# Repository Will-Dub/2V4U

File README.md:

# 2V4U

VCU, dashboard and documentation for an electric go-kart

## Overview

```
Software/            Dashboard and VCU code
Software/Dashboard   Qt dashboard
Software/VCU         VCU for an STM32G431
Software/VCU/Tests   Unit and integration tests
Hardware/            Schema of the VCU board
Docs/                Diagram and wiring
```

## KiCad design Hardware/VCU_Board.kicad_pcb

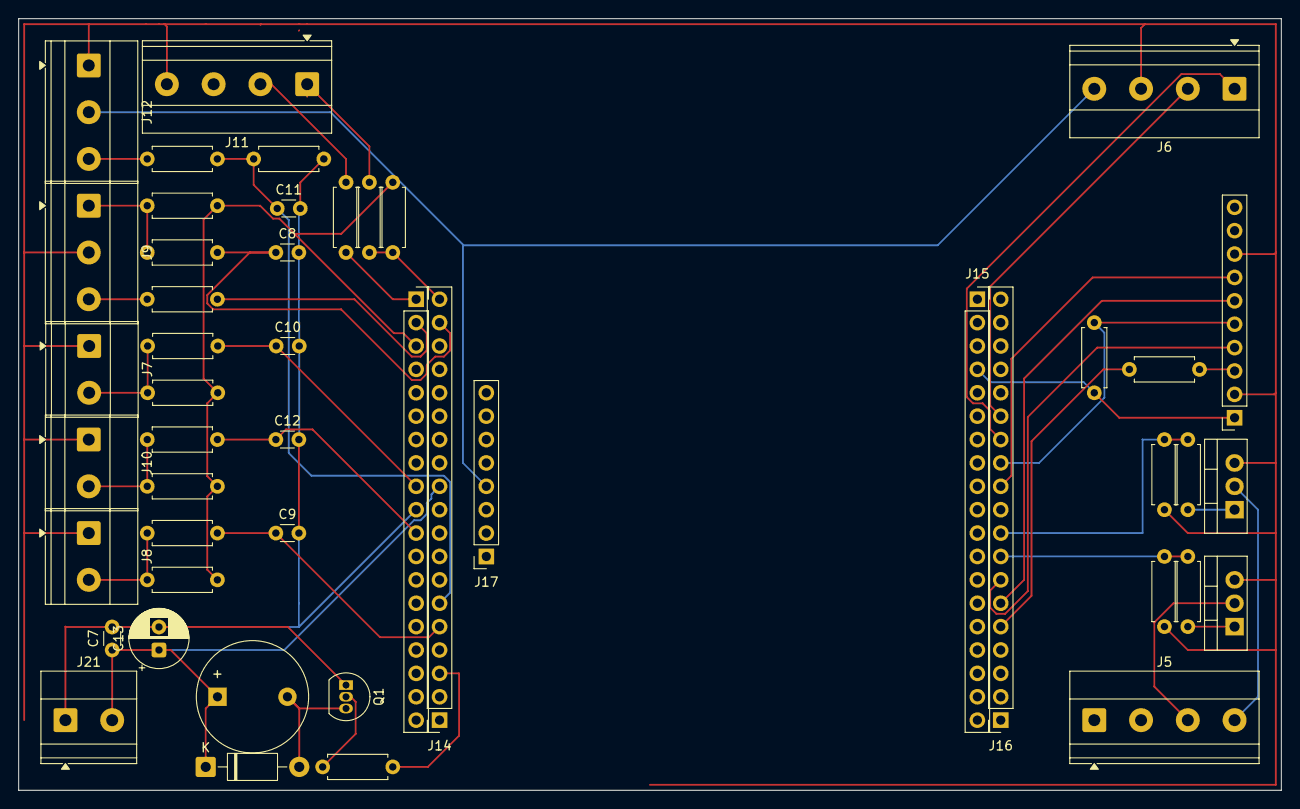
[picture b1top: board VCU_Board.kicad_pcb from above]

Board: 2 copper layers, 137.2 x 83.8 mm, 48 parts (0 on the bottom side), 36 nets.

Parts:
BZ1: Buzzer; Buzzer_12x9.5RM7.6
C7: 0.1μ; C_Disc_D3.0mm_W1.6mm_P2.50mm
C8, C9, C10, C11, C12: 100n; C_Disc_D3.0mm_W1.6mm_P2.50mm
C13: 10μ; CP_Radial_D6.3mm_P2.50mm
D4: D; D_DO-41_SOD81_P10.16mm_Horizontal
J3: ICM-20948; PinSocket_1x10_P2.54mm_Vertical
J5: Power Connector; TerminalBlock_Phoenix_MKDS-1,5-4-5.08_1x04_P5.08mm_Horizont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
J6: CAN Connector; TerminalBlock_Phoenix_MKDS-1,5-4-5.08_1x04_P5.08mm_Horizont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
J7: Direction Connector; TerminalBlock_Phoenix_MKDS-1,5-2-5.08_1x02_P5.08mm_Horizont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
J8: Brake Connector; TerminalBlock_Phoenix_MKDS-1,5-2-5.08_1x02_P5.08mm_Horizont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
J9: Sw Start Connector; TerminalBlock_Phoenix_MKDS-1,5-3-5.08_1x03_P5.08mm_Horizont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
J10: Emergency NO Connector; TerminalBlock_Phoenix_MKDS-1,5-2-5.08_1x02_P5.08mm_Horizont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
J11: BMS Connector; TerminalBlock_Phoenix_MKDS-1,5-4-5.08_1x04_P5.08mm_Horizont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
J12: Throttle Connector; TerminalBlock_Phoenix_MKDS-1,5-3-5.08_1x03_P5.08mm_Horizont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
J13, J14, J15, J16: Conn_01x19; PinSocket_1x19_P2.54mm_Vertical
J17: Conn_01x08; PinSocket_1x08_P2.54mm_Vertical
J21: Supply Connector; TerminalBlock_Phoenix_MKDS-1,5-2-5.08_1x02_P5.08mm_Horizont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
Q1: PN2222A; TO-92_Inline
Q3, Q4: MOSFET_CONTACTOR; TO-220-3_Vertical
R2, R20: 10000; R_Axial_DIN0207_L6.3mm_D2.5mm_P7.62mm_Horizontal
R3: 20000; R_Axial_DIN0207_L6.3mm_D2.5mm_P7.62mm_Horizontal
R4, R5, R6, R7, R19: 1000; R_Axial_DIN0207_L6.3mm_D2.5mm_P7.62mm_Horizontal
R8, R11, R13: 10k; R_Axial_DIN0207_L6.3mm_D2.5mm_P7.62mm_Horizontal
R9: 33; R_Axial_DIN0207_L6.3mm_D2.5mm_P7.62mm_Horizontal
R10: 270; R_Axial_DIN0207_L6.3mm_D2.5mm_P7.62mm_Horizontal
R12, R14: 100; R_Axial_DIN0207_L6.3mm_D2.5mm_P7.62mm_Horizontal
R15, R16, R17, R18: 2200; R_Axial_DIN0207_L6.3mm_D2.5mm_P7.62mm_Horizontal
R21, R22: 220; R_Axial_DIN0207_L6.3mm_D2.5mm_P7.62mm_Horizontal

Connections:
+3.3V: J3.1 (VCC), J13.3, J14.12, J15.4, J17.5, R4.1, R5.1, R6.1, R7.1, R8.1, R20.2
+5V: BZ1.1 (+), C7.1, C13.1, D4.1 (K), J6.4, J12.2, J14.11, J17.4, J21.2
/Driver/MOSFET_CONTACTOR_DRAIN: J5.3, Q4.2 (D)
/Driver/MOSFET_CONTACTOR_GATE: J16.8, R13.2, R14.1
/Driver/MOSFET_PRECHARGE_DRAIN: J5.4, Q3.2 (D)
/Driver/MOSFET_PRECHARGE_GATE: J16.9, R11.2, R12.1
/Interfaces/BMS_RX: J14.19, R20.1, R21.2
/Interfaces/BMS_TX: J13.1, R22.2
/Interfaces/BUZZER: J14.3, R19.2
/Interfaces/IMU_INT: J3.7 (INT), J16.11
/Interfaces/LED_SW_START: J13.2, R10.2
/Interfaces/SPI2_IMU_NCS: J3.5 (NCS), J16.12, R8.2
/Interfaces/SPI2_MISO: J3.6 (SDO), J16.6
/Interfaces/SPI2_MOSI: J3.4 (SDI), J16.7
/Interfaces/SPI2_SCK: J16.5, R9.1
/Interfaces/SW_BRAKE: C9.1, J14.5, R16.2
/Interfaces/SW_DIRECTION: C10.1, J13.9, R17.2
/Interfaces/SW_PUSH_EMERGENCY: C12.1, J13.11, R18.2
/Interfaces/SW_START: C8.1, J14.18, R15.1
/Interfaces/THROTTLE_ADC: C11.1, J14.6, R2.1, R3.1
/Off board high voltage/CAN_RX: J6.1, J16.13
/Off board high voltage/CAN_TX: J6.2, J16.14
GND: C7.2, C8.2, C9.2, C10.2, C11.2, C12.2, C13.2, J3.2 (GND), J3.8 (FSY), J6.3, J7.1, J8.1, J9.2, J10.1, J11.4, J12.1, J13.10, J14.9, J14.10, J14.16, J15.5, J16.4, J16.10, J17.2, J17.3, J21.1, Q1.1 (E), Q3.3 (S), Q4.3 (S), R3.2, R11.1, R13.1
unnamed: BZ1.2 (-), D4.2 (A), Q1.3 (C)
unnamed: J3.3 (SCLK), R9.2
unnamed: J7.2, R7.2, R17.1
unnamed: J8.2, R6.2, R16.1
unnamed: J9.1, R4.2, R15.2
unnamed: J9.3, R10.1
unnamed: J10.2, R5.2, R18.1
unnamed: J11.1, R21.1
unnamed: J11.2, R22.1
unnamed: J12.3, R2.2
unnamed: Q1.2 (B), R19.1
unnamed: Q3.1 (G), R12.2
unnamed: Q4.1 (G), R14.2

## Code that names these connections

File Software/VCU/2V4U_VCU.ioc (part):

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Mcu.Name=STM32G431R(6-8-B)Tx
Mcu.Package=LQFP64
Mcu.UserName=STM32G431RBTx
PA0.GPIOParameters=GPIO_Label
PA0.GPIO_Label=THROTTLE_ADC
PA0.Mode=IN1-Single-Ended
PA0.Signal=ADC1_IN1
PA1.GPIOParameters=GPIO_PuPd,GPIO_Label
PA1.GPIO_Label=SW_BRAKE
PA1.GPIO_PuPd=GPIO_PULLUP
PA1.Signal=GPIO_Input
PA11.GPIOParameters=GPIO_Label
PA11.GPIO_Label=CAN_RX
PA11.Mode=FDCAN_Activate
PA11.Signal=FDCAN1_RX
PA12.GPIOParameters=GPIO_Label
PA12.GPIO_Label=CAN_TX
PA12.Mode=FDCAN_Activate
PA12.Signal=FDCAN1_TX
PA13.GPIOParameters=GPIO_Label
PA13.GPIO_Label=T_SWDIO
PA13.Signal=SYS_JTMS-SWDIO
PA14.GPIOParameters=GPIO_Label
PA14.GPIO_Label=T_SWCLK
PA14.Signal=SYS_JTCK-SWCLK
PA15.GPIOParameters=GPIO_PuPd,GPIO_Label
PA15.GPIO_Label=SW_DIRECTION
PA15.GPIO_PuPd=GPIO_PULLUP
PA15.Signal=GPIO_Input
PA2.Mode=Asynchronous
PA2.Signal=LPUART1_TX
PA3.Mode=Asynchronous
PA3.Signal=LPUART1_RX
PA5.GPIOParameters=GPIO_Label
PA5.GPIO_Label=LED_BOARD
PA5.Signal=GPIO_Output
PB0.GPIOParameters=GPIO_Label
PB0.GPIO_Label=BUZZER
PB0.Signal=GPIO_Output
PB1.GPIOParameters=GPIO_Label
PB1.GPIO_Label=MOSFET_CONTACTOR_GATE
PB1.Signal=GPIO_Output
PB11.GPIOParameters=GPIO_Label
PB11.GPIO_Label=IMU_INT
PB11.Signal=GPXTI11
PB12.GPIOParameters=GPIO_Speed,PinState,GPIO_PuPd,GPIO_Label
PB12.GPIO_Label=SPI2_IMU_NCS
PB12.GPIO_PuPd=GPIO_PULLUP
PB12.GPIO_Speed=GPIO_SPEED_FREQ_VERY_HIGH
PB12.PinState=GPIO_PIN_SET
PB12.Signal=GPIO_Output
PB13.Mode=Full_Duplex_Master
PB13.Signal=SPI2_SCK
PB14.Mode=Full_Duplex_Master
PB14.Signal=SPI2_MISO
PB15.Mode=Full_Duplex_Master
PB15.Signal=SPI2_MOSI
PB2.GPIOParameters=GPIO_Label
PB2.GPIO_Label=MOSFET_PRECHARGE_GATE
PB2.Signal=GPIO_Output
PB3.GPIOParameters=GPIO_Label
PB3.GPIO_Label=T_SWO
PB3.Signal=SYS_JTDO-SWO
PB7.GPIOParameters=GPIO_PuPd,GPIO_Label
PB7.GPIO_Label=SW_PUSH_EMERGENCY
PB7.GPIO_PuPd=GPIO_PULLUP
PB7.Signal=GPIO_Input
PC10.GPIOParameters=GPIO_Label
PC10.GPIO_Label=BMS_TX
PC10.Mode=Asynchronous
PC10.Signal=UART4_TX
PC11.GPIOParameters=GPIO_Label
PC11.GPIO_Label=BMS_RX
PC11.Mode=Asynchronous
PC11.Signal=UART4_RX
PC12.GPIOParameters=GPIO_Label
PC12.GPIO_Label=LED_SW_START
PC12.Signal=GPIO_Output
PC13.GPIOParameters=GPIO_PuPd,GPIO_Label
PC13.GPIO_Label=BTN_BOARD
PC13.GPIO_PuPd=GPIO_PULLDOWN
PC13.Signal=GPIO_Input
PC14-OSC32_IN.GPIOParameters=GPIO_Label
PC14-OSC32_IN.GPIO_Label=RCC_OSC32_OUT
PC14-OSC32_IN.Signal=RCC_OSC32_IN
PC15-OSC32_OUT.GPIOParameters=GPIO_Label
PC15-OSC32_OUT.GPIO_Label=RCC_OSC32_OUT
PC15-OSC32_OUT.Signal=RCC_OSC32_OUT
PD2.GPIOParameters=GPIO_PuPd,GPIO_Label
PD2.GPIO_Label=SW_START
PD2.GPIO_PuPd=GPIO_PULLUP
PD2.Signal=GPIO_Input
PF0-OSC_IN.GPIOParameters=GPIO_Label
PF0-OSC_IN.GPIO_Label=RCC_OSC_IN
PF0-OSC_IN.Signal=RCC_OSC_IN
PF1-OSC_OUT.GPIOParameters=GPIO_Label
PF1-OSC_OUT.GPIO_Label=RCC_OSC_OUT
PF1-OSC_OUT.Signal=RCC_OSC_OUT
RCC.HSE_VALUE=24000000
RCC.SYSCLKFreq_VALUE=170000000
RCC.SYSCLKSource=RCC_SYSCLKSOURCE_PLLCLK
board=NUCLEO-G431RB
boardIOC=true
